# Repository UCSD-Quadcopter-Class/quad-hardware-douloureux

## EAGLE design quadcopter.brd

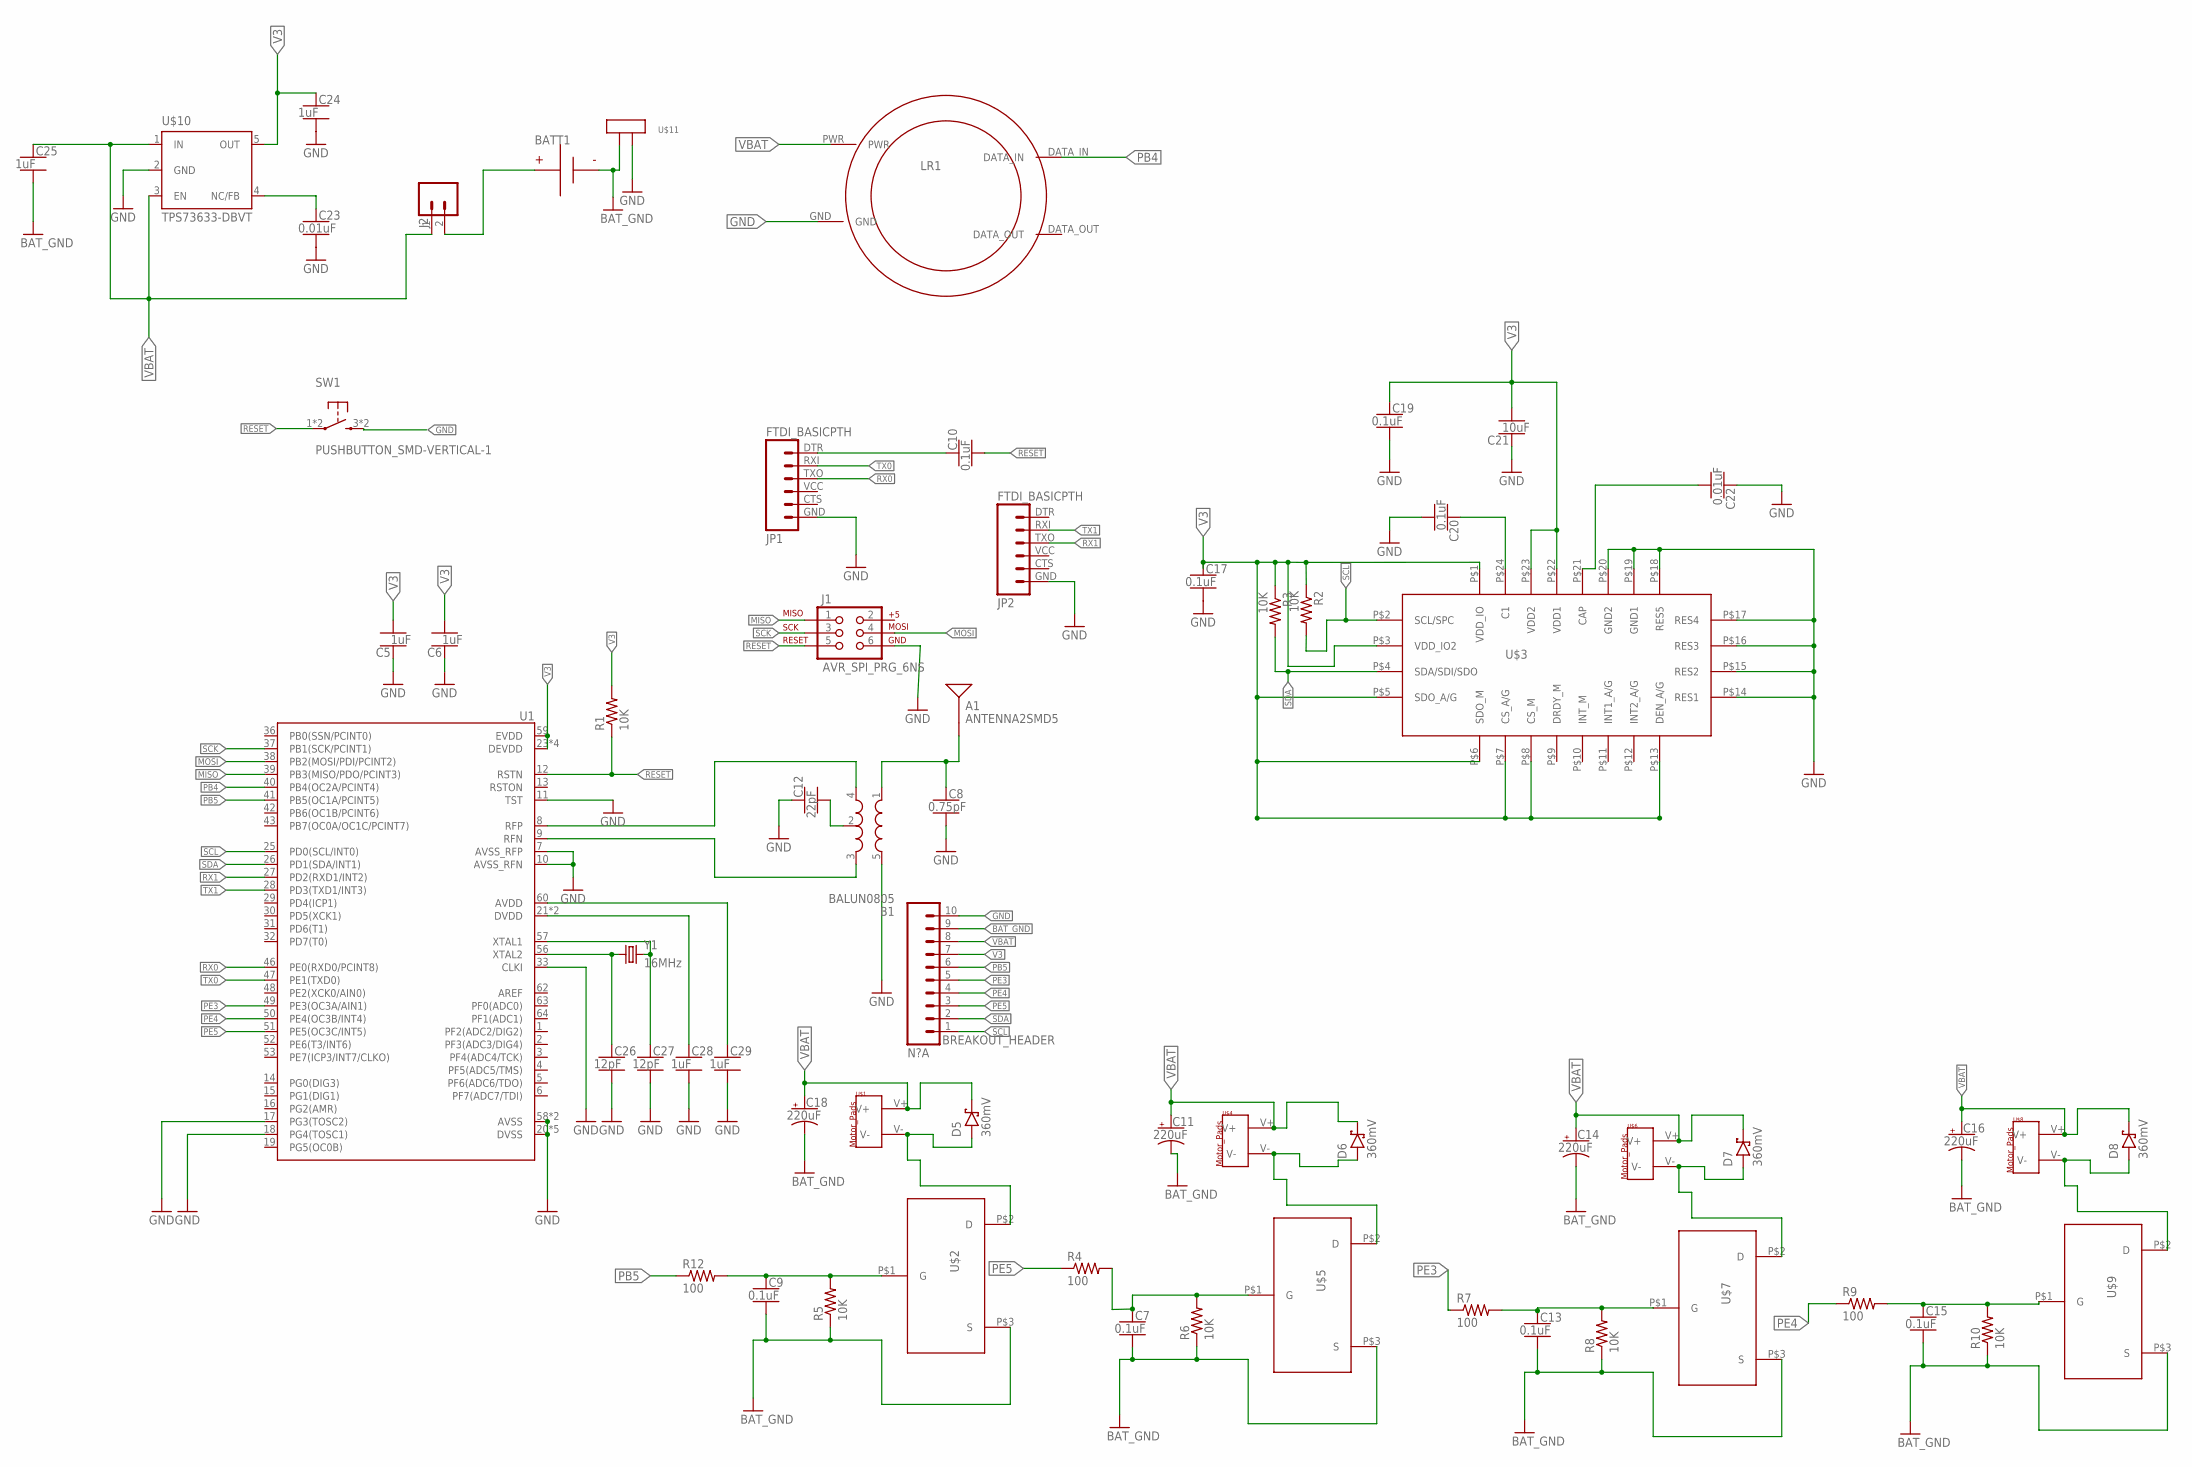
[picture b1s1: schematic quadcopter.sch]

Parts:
A1: ANTENNA2SMD5; ANTENNA-CHIP5
B1: BALUN0805; BALUN
BATT1: BATTERY-HUBSAN-W/HOLDER; BATTERY-W/HOLDER-380MAH-HUBSAN
BREAKOUT_HEADER: N?A; HDRV10W63P254_10X1_2540X254H838_HS
C5, C6, C24, C25, C28, C29: 1uF; CAPC2012X140_HS
C7, C9, C13, C15: 0.1uF; CERAMIC_CAP_0805
C8: 0.75pF; CAPC2012X140_HS
C10, C17, C19, C20: 0.1uF; CAPC2012X140_HS
C11, C14, C16, C18: 220uF; CAPMP7343X310_HS
C12: 22pF; CAPC2012X140_HS
C21: 10uF; CAPC2012X140_HS
C22, C23: 0.01uF; CAPC2012X140_HS
C26, C27: 12pF; CAPC2012X140_HS
D5, D6, D7, D8: 360mV; SOD3716X135_HS
J1: AVR_SPI_PRG_6NS; 2X3-NS
J2: MALE_HEADER_2POS-2X1-0.1IN; MALE_HEADER_2X1_0.1IN
JP1, JP2: FTDI_BASICPTH; FTDI_BASIC
LR1: LED_RING
R1, R2, R3, R5, R6, R8, R10: 10K; RESC2012X60_HS
R4, R7, R9, R12: 100; RESC2012X60_HS
SW1: PUSHBUTTON_SMD-VERTICAL-1; TE_FSM8JSMA_HS
U1: ATMEGA128RFA1; QFN-64
U$1, U$4, U$6, U$8: MOTOR_PADS
U$2, U$5, U$7, U$9: N-CHANNEL_MOSFET; N-CHANNELMOFSET
U$3: 9-AXIS_IMU
U$10: TPS73633-DBVT; SOT23-DBV
U$11: NET_BRIDGE
Y1: 16MHz; CRYSTAL-SMD-5X3

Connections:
BAT_GND: BATT1.- (N), BREAKOUT_HEADER.9, C7.2, C9.2, C11.2 (-), C13.2, C14.2 (-), C15.2, C16.2 (-), C18.2 (-), C25.2, R5.1, R6.1, R8.1, R10.1, U$2.P$3 (S), U$5.P$3 (S), U$7.P$3 (S), U$9.P$3 (S), U$11.P$1
GND: B1.5 (GND), BREAKOUT_HEADER.10, C5.1, C6.1, C8.2, C12.1, C17.2, C19.2, C20.2, C21.1, C22.1, C23.2, C24.2, C26.2, C27.2, C28.2, C29.2, J1.6, JP1.GND (6), JP2.GND (6), LR1.GND, SW1.3 (2), SW1.4 (2), U1.7 (AVSS_RFP), U1.10 (AVSS_RFN), U1.11 (TST), U1.17 (PG3(TOSC2)), U1.18 (PG4(TOSC1)), U1.20 (DVSS), U1.24 (DVSS), U1.33 (CLKI), U1.35 (DVSS), U1.45 (DVSS), U1.55 (DVSS), U1.58 (AVSS), U1.61 (AVSS), U$3.P$14 (RES1), U$3.P$15 (RES2), U$3.P$16 (RES3), U$3.P$17 (RES4), U$3.P$18 (RES5), U$3.P$19 (GND1), U$3.P$20 (GND2), U$10.2 (GND), U$11.P$2
MISO: J1.1, U1.39 (PB3(MISO/PDO/PCINT3))
MOSI: J1.4, U1.38 (PB2(MOSI/PDI/PCINT2))
unnamed: C9.1, R5.2, R12.2, U$2.P$1 (G)
unnamed: C7.1, R4.2, R6.2, U$5.P$1 (G)
unnamed: A1.FEED, B1.1 (IN), C8.1
unnamed: B1.2 (GND), C12.2
unnamed: C10.1, JP1.DTR (1)
unnamed: D6.A, U$4.V-, U$5.P$2 (D)
unnamed: C13.1, R7.2, R8.2, U$7.P$1 (G)
unnamed: D5.A, U$1.V-, U$2.P$2 (D)
unnamed: D7.A, U$6.V-, U$7.P$2 (D)
unnamed: C15.1, R9.2, R10.2, U$9.P$1 (G)
unnamed: D8.A, U$8.V-, U$9.P$2 (D)
unnamed: C20.1, U$3.P$24 (C1)
unnamed: C22.2, U$3.P$21 (CAP)
unnamed: C26.1, U1.56 (XTAL2), Y1.1
unnamed: BATT1.+, J2.2
unnamed: C23.1, U$10.4 (NC/FB)
unnamed: B1.4 (OUT1), U1.8 (RFP)
unnamed: B1.3 (OUT2), U1.9 (RFN)
unnamed: C29.1, U1.60 (AVDD)
unnamed: C28.1, U1.21 (DVDD), U1.22 (DVDD)
unnamed: C27.1, U1.57 (XTAL1), Y1.3 (2)
PB4: LR1.DATA_IN, U1.40 (PB4(OC2A/PCINT4))
PB5: BREAKOUT_HEADER.6, R12.1, U1.41 (PB5(OC1A/PCINT5))
PE3: BREAKOUT_HEADER.5, R7.1, U1.49 (PE3(OC3A/AIN1))
PE4: BREAKOUT_HEADER.4, R9.1, U1.50 (PE4(OC3B/INT4))
PE5: BREAKOUT_HEADER.3, R4.1, U1.51 (PE5(OC3C/INT5))
RESET: C10.2, J1.5, R1.1, SW1.1, SW1.2 (1), U1.12 (RSTN)
RX0: JP1.TXO (3), U1.46 (PE0(RXD0/PCINT8))
RX1: JP2.TXO (3), U1.27 (PD2(RXD1/INT2))
SCK: J1.3, U1.37 (PB1(SCK/PCINT1))
SCL: BREAKOUT_HEADER.1, R2.2, U1.25 (PD0(SCL/INT0)), U$3.P$2 (SCL/SPC)
SDA: BREAKOUT_HEADER.2, R3.2, U1.26 (PD1(SDA/INT1)), U$3.P$4 (SDA/SDI/SDO)
TX0: JP1.RXI (2), U1.47 (PE1(TXD0))
TX1: JP2.RXI (2), U1.28 (PD3(TXD1/INT3))
V3: BREAKOUT_HEADER.7, C5.2, C6.2, C17.1, C19.1, C21.2, C24.1, R1.2, R2.1, R3.1, U1.23 (DEVDD), U1.34 (DEVDD), U1.44 (DEVDD), U1.54 (DEVDD), U1.59 (EVDD), U$3.P$1 (VDD_IO), U$3.P$3 (VDD_IO2), U$3.P$5 (SDO_A/G), U$3.P$6 (SDO_M), U$3.P$7 (CS_A/G), U$3.P$8 (CS_M), U$3.P$13 (DEN_A/G), U$3.P$22 (VDD1), U$3.P$23 (VDD2), U$10.5 (OUT)
VBAT: BREAKOUT_HEADER.8, C11.1 (+), C14.1 (+), C16.1 (+), C18.1 (+), C25.1, D5.C, D6.C, D7.C, D8.C, J2.1, LR1.PWR, U$1.V+, U$4.V+, U$6.V+, U$8.V+, U$10.1 (IN), U$10.3 (EN)

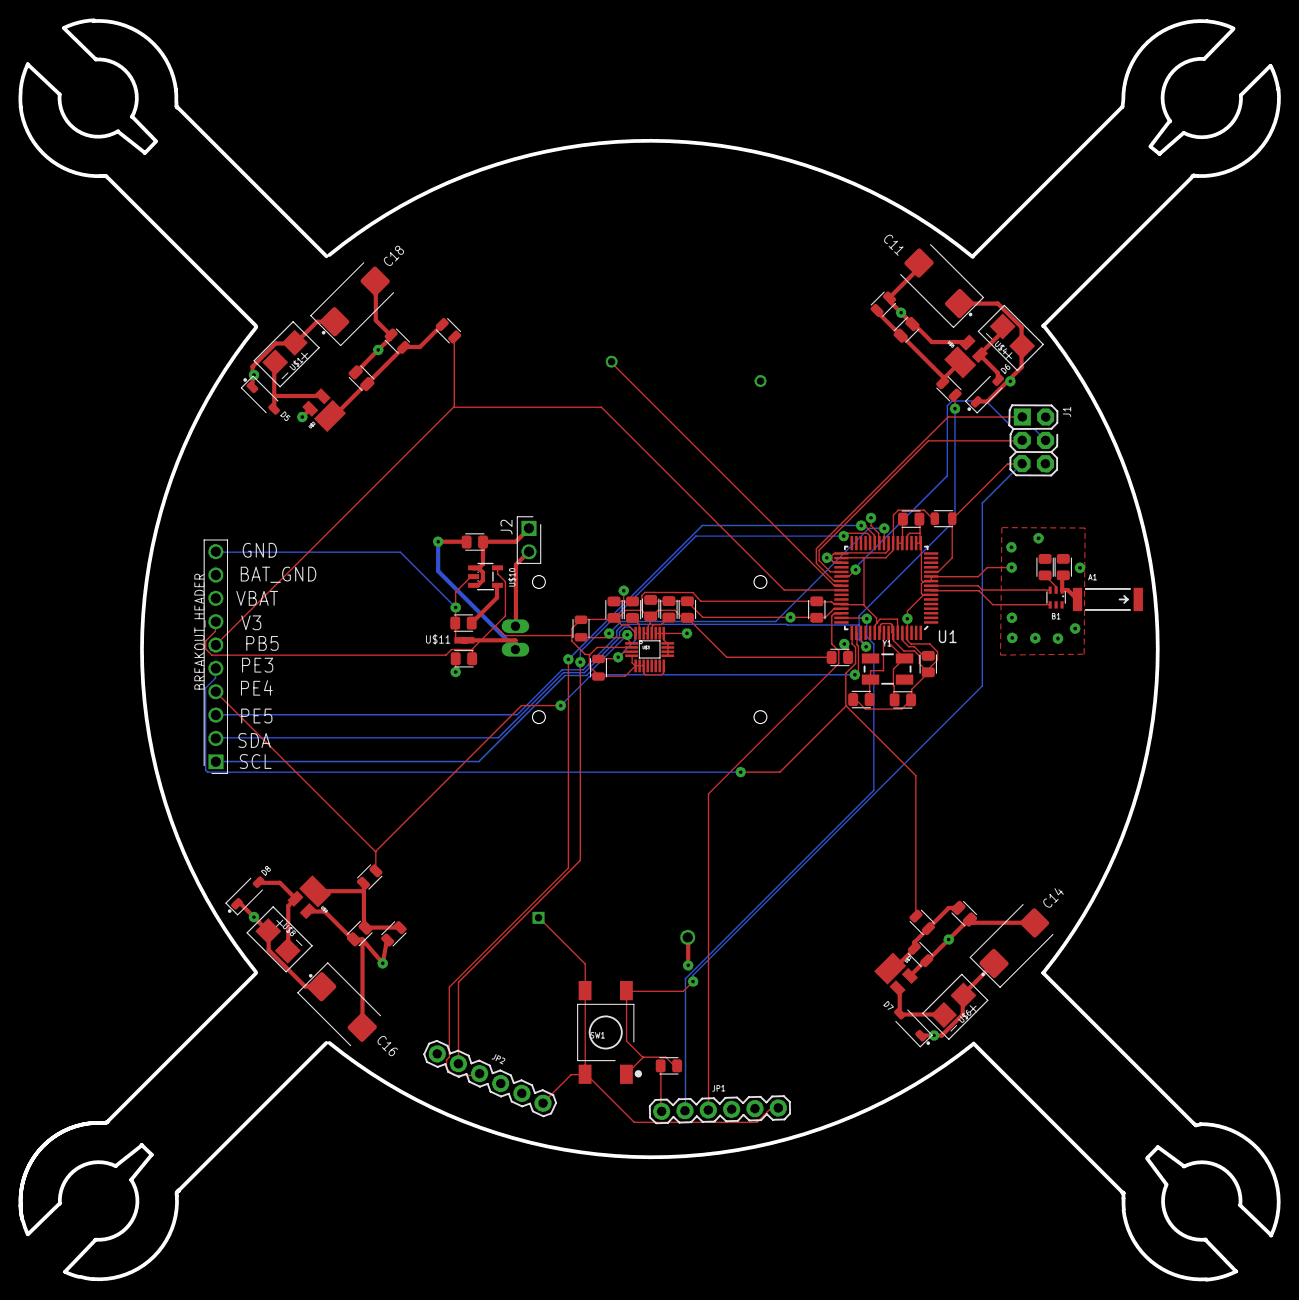
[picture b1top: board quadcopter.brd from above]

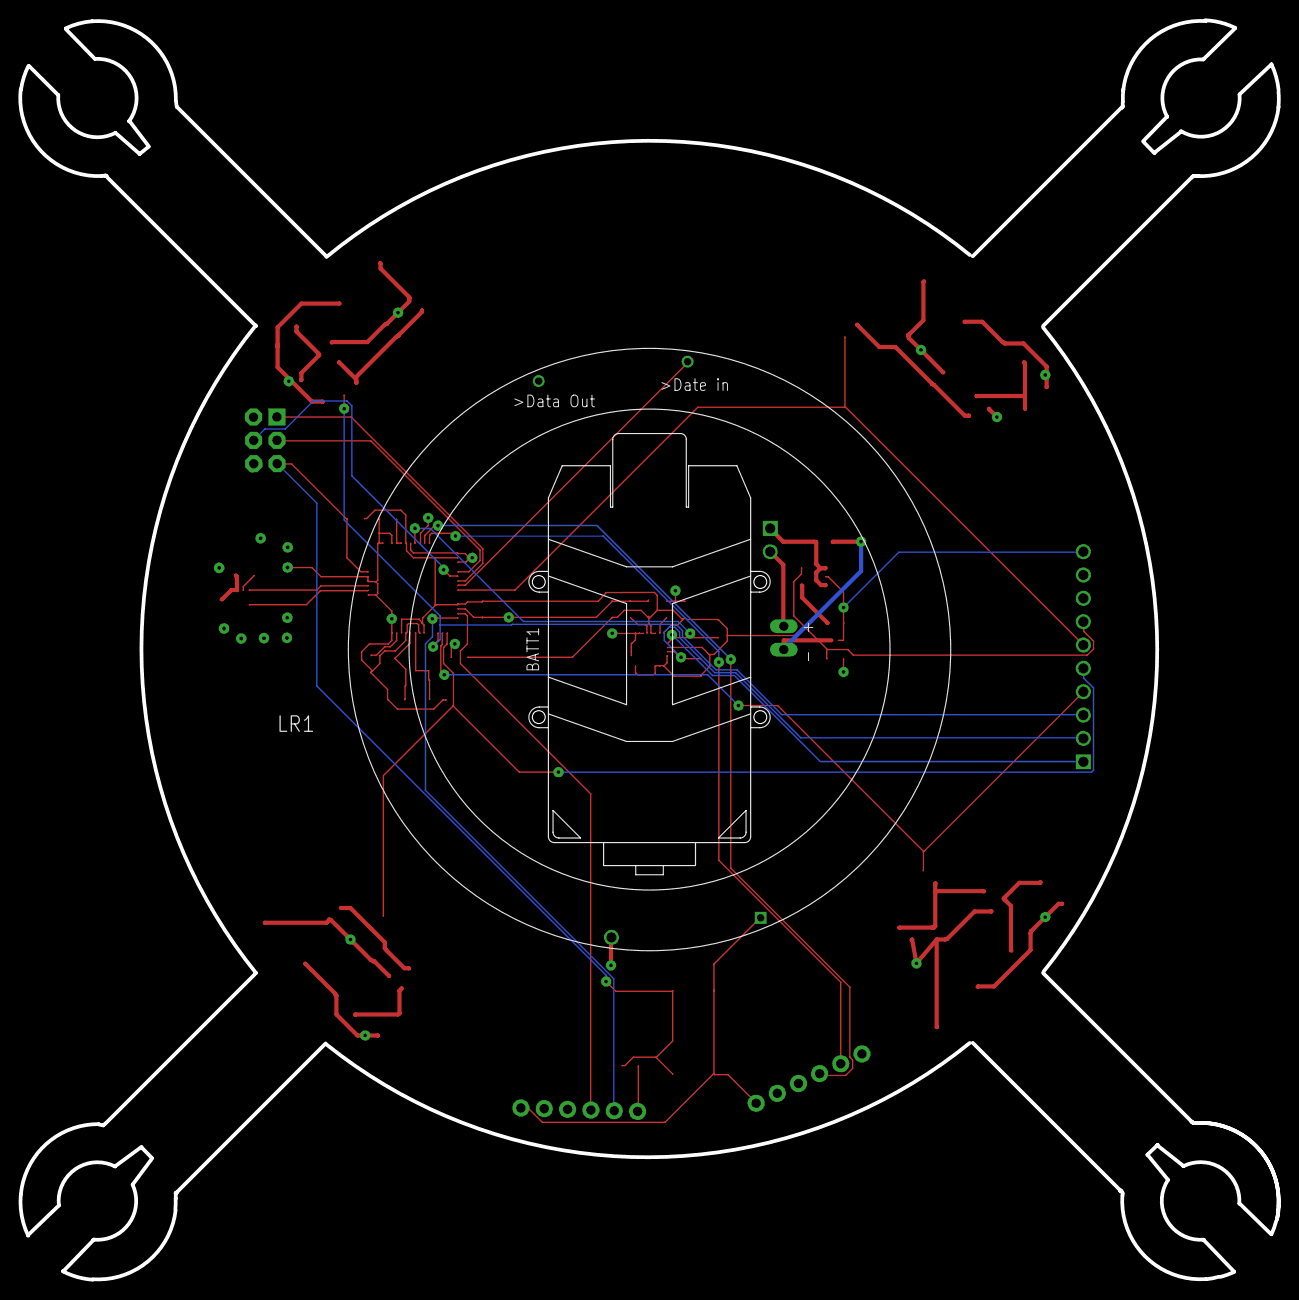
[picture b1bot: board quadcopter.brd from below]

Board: 4 copper layers, 136.9 x 137.0 mm, 63 parts (2 on the bottom side), 40 nets.

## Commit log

2017-04-15 Zhe's Lib
2017-04-15 Jason's Library
2017-04-17 Add files via upload
    This is who am i file made by Zhe Wang not Jason Wong
2017-04-18 Updated Zhe's lbr schematic
2017-04-18 Upload quardparts schematic
2017-04-18 Update MFSET
2017-04-19 Update quadparts
2017-04-19 Finished Microcontroller, will be working on motors next
2017-04-19 Calling it a day
2017-04-20 Did I tag? Submitting for Lab 4
2017-04-20 change switch to male header
2017-04-25 a lot of updtes
2017-04-25 Changes to Schematic
2017-04-25 Finished schematic review, tagging next
2017-04-25 add net bridge
2017-04-25 Fixed all connections, still need to change LEDs and give values to pieces
2017-04-25 change libraries
2017-04-25 Updated libraries and also put in net bridge
2017-04-27 instructior review of original schematic
2017-04-27 Current schematic
2017-04-27 push an updata
2017-04-27 Updated IMU
2017-04-30 Fixed junctions and pull up resistor
2017-04-30 updated schematic review
2017-05-01 first draft of board design
2017-05-02 Finished Professor's review
2017-05-02 add new led ring
2017-05-02 Life is so hard
2017-05-02 I did push
2017-05-02 Not sure what I changed here
2017-05-02 ... Zhe help I'm not sure how to fix the board
2017-05-02 fix everything
2017-05-02 minor fix the board
2017-05-04 Board design reviews
2017-05-07 Renamed schematics
2017-05-07 Moved parts around on board, trying to connect air wires
2017-05-07 Trying to fix air wires
2017-05-07 fix prebuid library
2017-05-07 Curently updating
2017-05-07 fix prebuilt library
2017-05-07 Polygon
2017-05-07 fix jason library
2017-05-07 prebuilt library fixed
2017-05-07 Yay 5 air wires and less erorrs
2017-05-08 Almsot done with board
2017-05-08 Currently fixing width issues
2017-05-08 Changes to library
2017-05-08 board
2017-05-09 Finished All Air-wires, the remaining airwires are already connected yet wishes to connect to others of the same connection. Need to ask
2017-05-09 No more errorsgit add quadcopter.brd
2017-05-11 Fixed some library issues and also updates for new DRC file
2017-05-11 fix librares
2017-05-11 safjafhaoeifhoei
2017-05-14 more schematic comments from swanson
2017-05-15 Finished Board and Passed FREEDFM
2017-05-16 Tapeout
2017-05-16 deleted files from git
2017-05-16 Board comments from swanson
2017-05-17 Changes from first board review
2017-05-18 fix mosfet
2017-05-18 Last update
2017-05-18 Done?
